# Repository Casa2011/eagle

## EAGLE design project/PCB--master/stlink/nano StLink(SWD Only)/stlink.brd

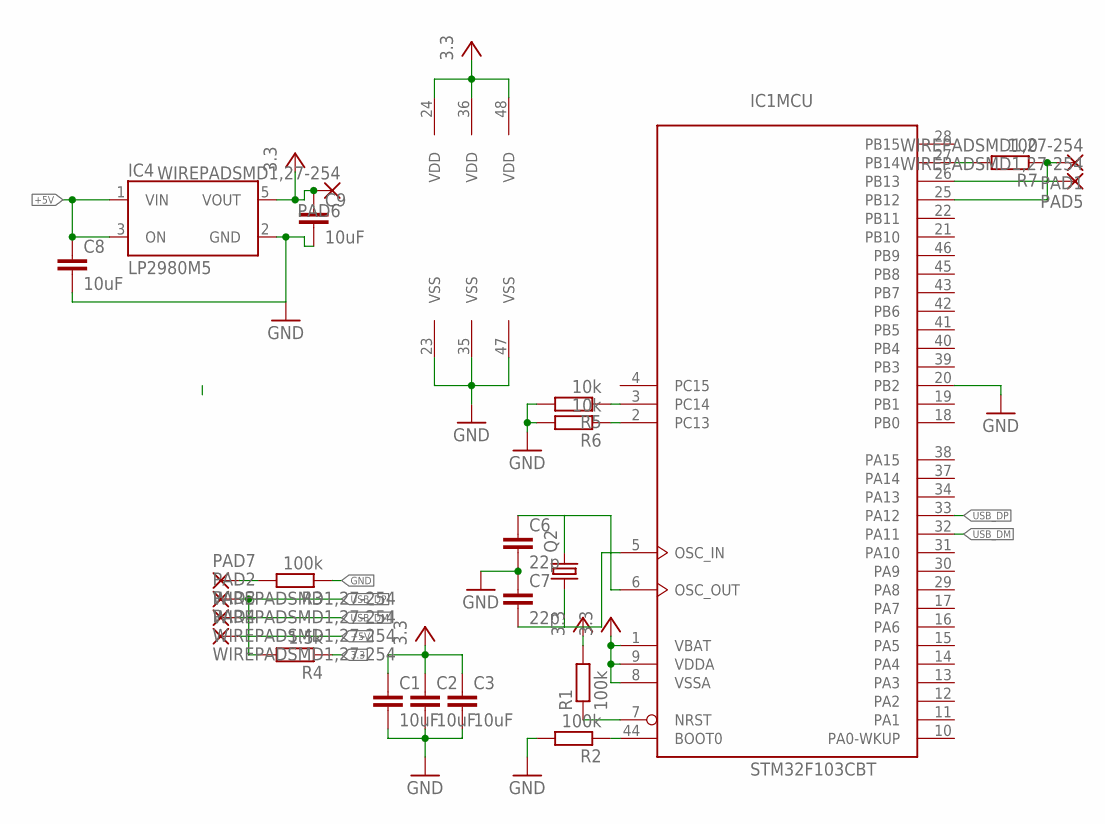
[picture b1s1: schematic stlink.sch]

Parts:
C1, C2, C3, C8, C9: 10uF; C0805
C6, C7: 22p; C0805
IC1: STM32F103CBT; LQFP48
IC4: LP2980M5; SOT23-5
PAD1, PAD2, PAD3, PAD4, PAD5, PAD6, PAD7: WIREPADSMD1,27-254; SMD1,27-2,54
Q2: CRYSTALCTS406; CTS406
R1, R2, R3: 100k; R0805
R4: 1.5k; R0805
R5, R6: 10k; R0805
R7: 100; R0805

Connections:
3.3: R4.1
+5V: C8.1, IC4.1 (VIN), IC4.3 (ON), PAD4.1
GND: C1.2, C2.2, C3.2, C6.2, C7.1, C8.2, C9.2, IC1.20 (PB2), IC1.23 (VSS), IC1.35 (VSS), IC1.47 (VSS), IC4.2 (GND), R2.2, R3.1, R5.2, R6.2
unnamed: C6.1, IC1.6 (OSC_OUT), Q2.3 (2)
unnamed: IC1.7 (NRST), R1.1
unnamed: C7.2, IC1.5 (OSC_IN), Q2.1
unnamed: IC1.44 (BOOT0), R2.1
unnamed: IC1.27 (PB14), R7.2
unnamed: IC1.26 (PB13), PAD5.1
unnamed: PAD7.1, R3.2
unnamed: IC1.3 (PC14), R5.1
unnamed: IC1.2 (PC13), R6.1
unnamed: IC1.25 (PB12), PAD1.1, R7.1
USB_DM: IC1.32 (PA11), PAD3.1
USB_DP: IC1.33 (PA12), PAD2.1, R4.2
VCC: C1.1, C2.1, C3.1, C9.1, IC1.1 (VBAT), IC1.8 (VSSA), IC1.9 (VDDA), IC1.24 (VDD), IC1.36 (VDD), IC1.48 (VDD), IC4.5 (VOUT), PAD6.1, R1.2

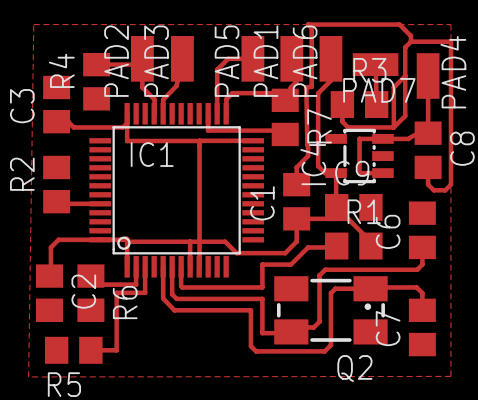
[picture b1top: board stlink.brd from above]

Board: 2 copper layers, 24 parts (0 on the bottom side), 15 nets.

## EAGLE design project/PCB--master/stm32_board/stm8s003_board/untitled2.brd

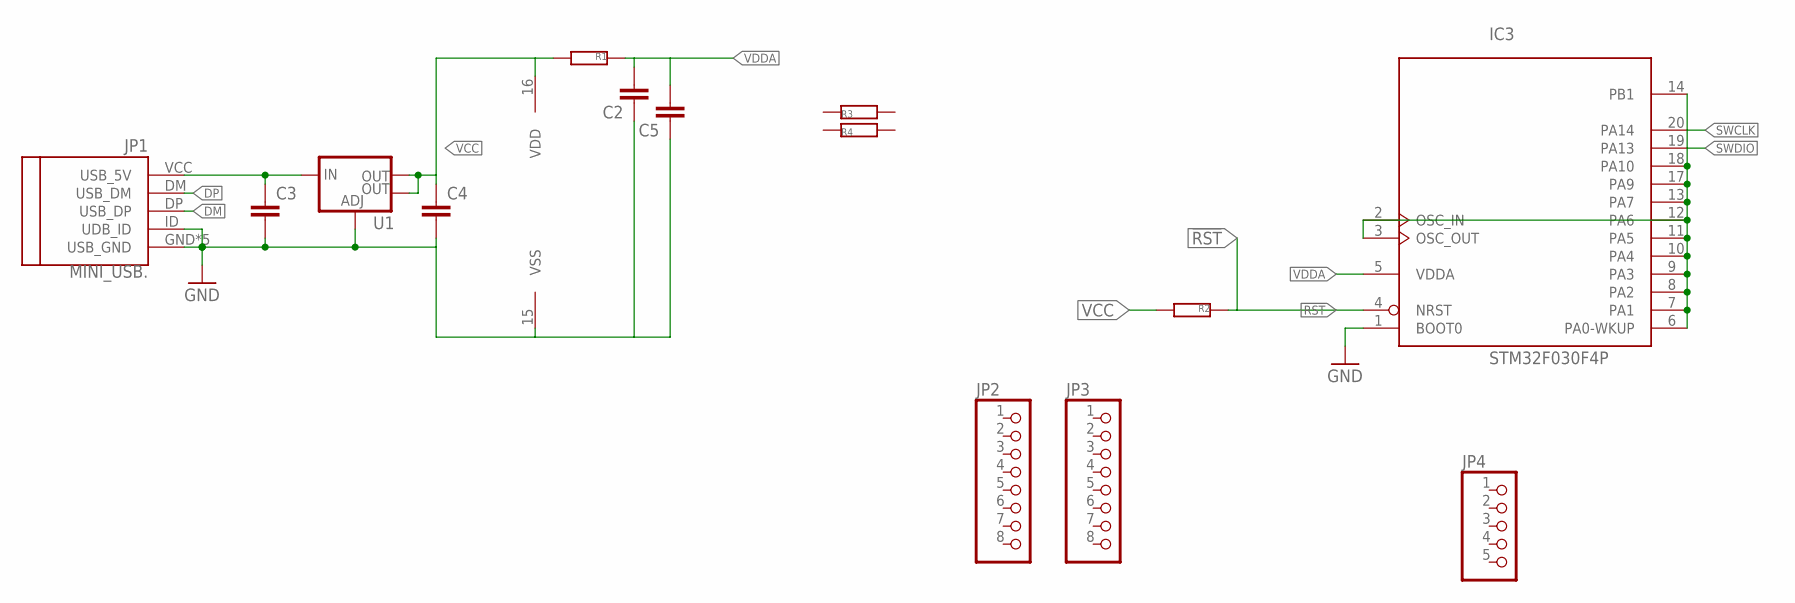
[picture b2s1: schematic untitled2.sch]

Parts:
C2, C3, C4, C5: CC0805; C0805
IC3: STM32F030F4P; TSSOP20-I
JP1: MINI_USB.; 32005-201
JP2, JP3: PINHD-1X08_2.54; 1X08
JP4: PINHD-1X05_2.54; 1X05
R1, R2: R0603; 0603
R3, R4: R0805
U1: V_REG_LM1117SOT223; SOT223

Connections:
5V: C3.1, JP1.VCC (USB_5V), U1.3 (IN)
!RST: IC3.4 (NRST), R2.1
DM: JP1.DP (USB_DP)
DP: JP1.DM (USB_DM)
GND: C2.1, C3.2, C4.2, C5.1, IC3.1 (BOOT0), IC3.15 (VSS), JP1.GND (USB_GND), JP1.ID (UDB_ID), JP1.M1 (USB_GND), JP1.M2 (USB_GND), JP1.M3 (USB_GND), JP1.M4 (USB_GND), U1.1 (ADJ)
unnamed: IC3.2 (OSC_IN), IC3.3 (OSC_OUT), IC3.6 (PA0-WKUP), IC3.7 (PA1), IC3.8 (PA2), IC3.9 (PA3), IC3.10 (PA4), IC3.11 (PA5), IC3.12 (PA6), IC3.13 (PA7), IC3.14 (PB1), IC3.17 (PA9), IC3.18 (PA10)
SWCLK: IC3.20 (PA14)
SWDIO: IC3.19 (PA13)
VCC: C4.1, IC3.16 (VDD), R1.2, R2.2, U1.2 (OUT), U1.4 (OUT)
VDDA: C2.2, C5.2, IC3.5 (VDDA), R1.1

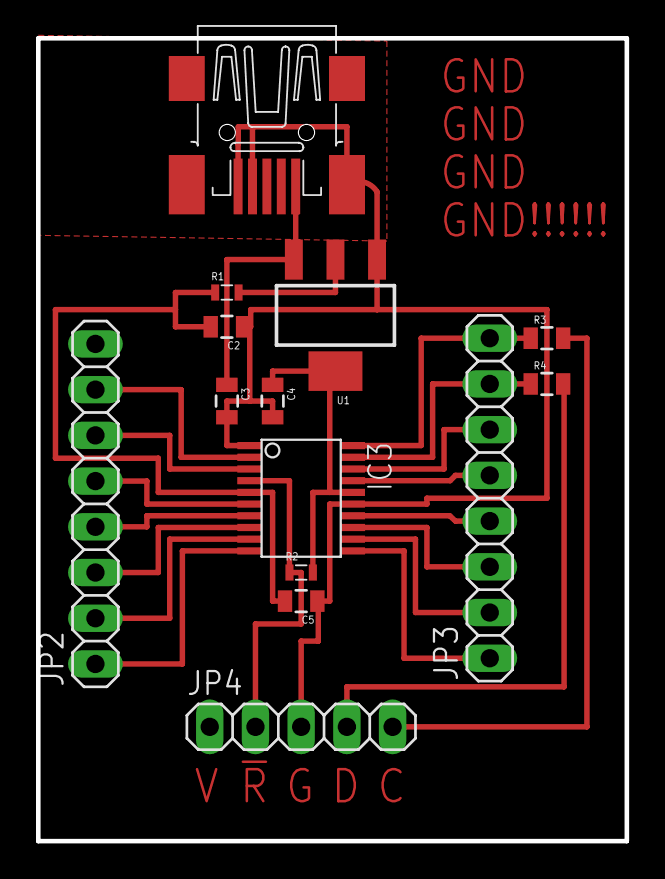
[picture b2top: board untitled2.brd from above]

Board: 2 copper layers, 32.7 x 44.6 mm, 14 parts (0 on the bottom side), 6 nets.

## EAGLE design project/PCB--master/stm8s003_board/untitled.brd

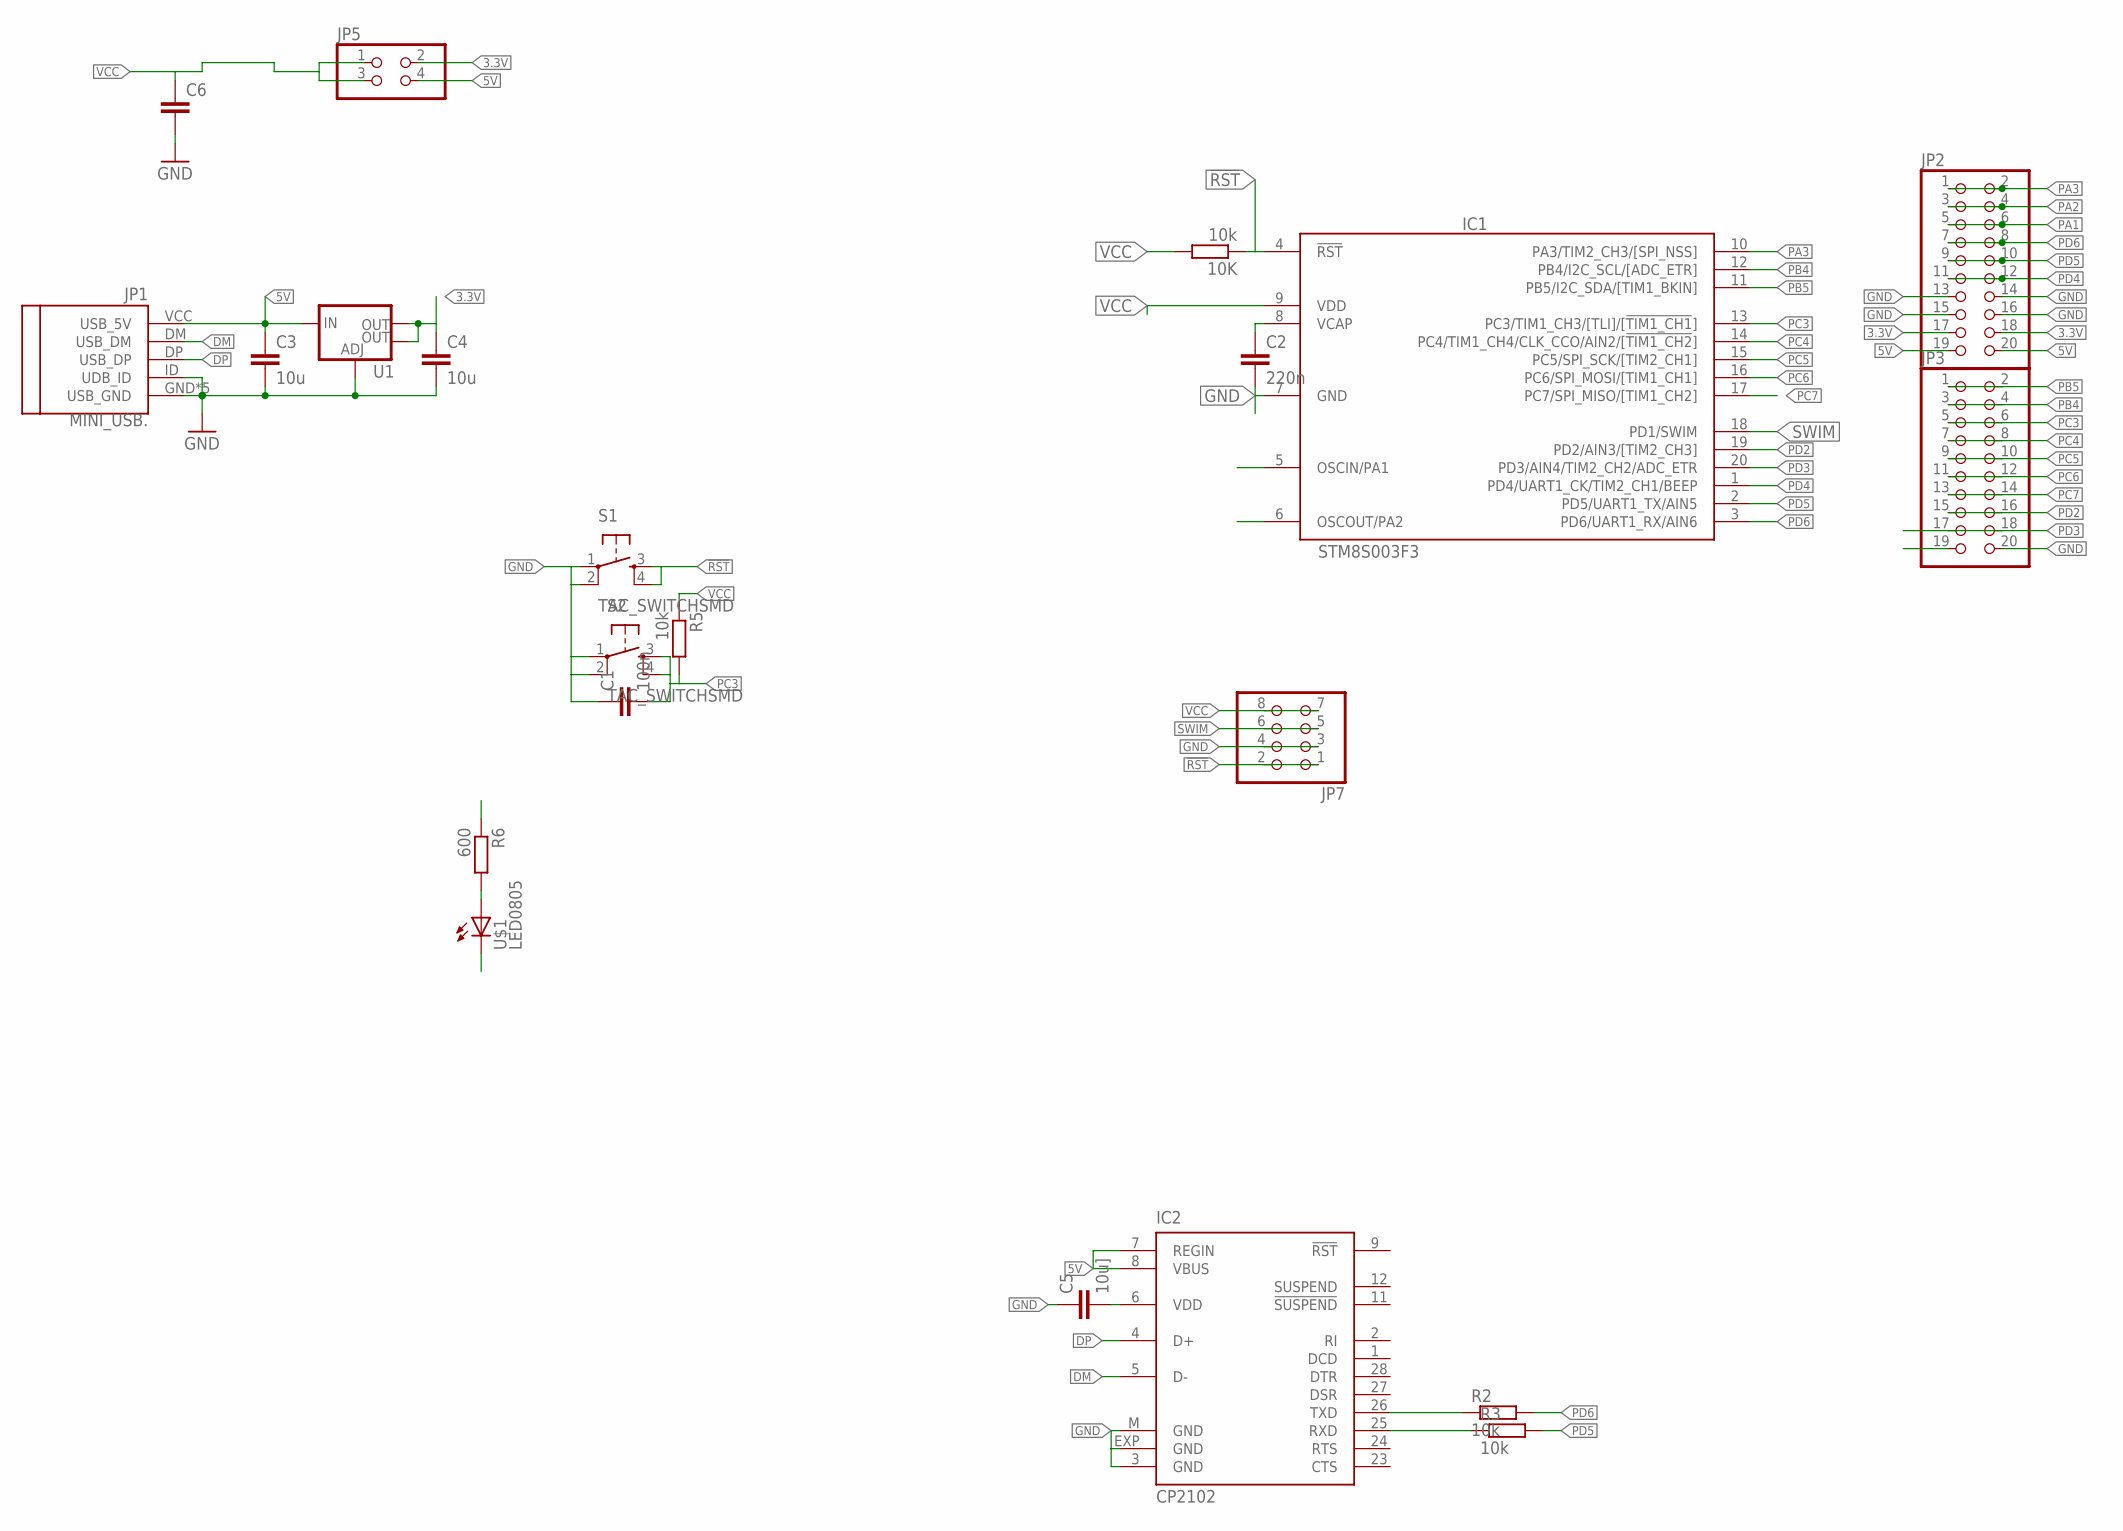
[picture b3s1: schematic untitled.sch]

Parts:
10K: 10k; 0603
C1: 100n; C0805
C2: 220n; C0603
C3, C4: 10u; C0805
C5: 10u]; C0603
C6: CC0805; C0805
IC1: STM8S003F3; TSSOP20
IC2: CP2102; MLP28
JP1: MINI_USB.; 32005-201
JP2, JP3: PINHD-2X10_2.54-SMD; 2X10SMD
JP5: PINHD-2X02_2.54-SMD; 2X02SMD
JP7: PINHD-2X04_2.54-SMD; 2X04SMD
R2, R3, R5: 10k; 0603
R6: 600; 0603
S1, S2: TAC_SWITCHSMD; TACTILE-SWITCH-SMD
U1: V_REG_LM1117SOT223; SOT223
U$1: LED0805; 0805-LED

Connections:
1: IC2.26 (TXD), R2.1
2: IC2.25 (RXD), R3.1
3.3V: C4.1, JP2.17, JP2.18, JP5.2, U1.2 (OUT), U1.4 (OUT)
5V: C3.1, IC2.7 (REGIN), IC2.8 (VBUS), JP1.VCC (USB_5V), JP2.19, JP2.20, JP5.4, U1.3 (IN)
!RST: 10K.1, IC1.4 (!RST), JP7.1, JP7.2, S1.3, S1.4
DM: IC2.5 (D-), JP1.DM (USB_DM)
DP: IC2.4 (D+), JP1.DP (USB_DP)
GND: C1.1, C2.2, C3.2, C4.2, C5.1, C6.2, IC1.7 (GND), IC2.3 (GND), IC2.EXP (GND), IC2.M (GND), JP1.GND (USB_GND), JP1.ID (UDB_ID), JP1.M1 (USB_GND), JP1.M2 (USB_GND), JP1.M3 (USB_GND), JP1.M4 (USB_GND), JP2.13, JP2.14, JP2.15, JP2.16, JP3.19, JP3.20, JP7.3, JP7.4, S1.1, S1.2, S2.1, S2.2, U1.1 (ADJ), U$1.C
unnamed: C2.1, IC1.8 (VCAP)
unnamed: C5.2, IC2.6 (VDD)
unnamed: R6.2, U$1.A
PA1: IC1.5 (OSCIN/PA1), JP2.5, JP2.6
PA2: IC1.6 (OSCOUT/PA2), JP2.3, JP2.4
PA3: IC1.10 (PA3/TIM2_CH3/[SPI_NSS]), JP2.1, JP2.2
PB4: IC1.12 (PB4/I2C_SCL/[ADC_ETR]), JP3.3, JP3.4
PB5: IC1.11 (PB5/I2C_SDA/[TIM1_BKIN]), JP3.1, JP3.2
PC3: C1.2, IC1.13 (PC3/TIM1_CH3/[TLI]/[!TIM1_CH1!]), JP3.5, JP3.6, R5.2, S2.3, S2.4
PC4: IC1.14 (PC4/TIM1_CH4/CLK_CCO/AIN2/[!TIM1_CH2!]), JP3.7, JP3.8
PC5: IC1.15 (PC5/SPI_SCK/[TIM2_CH1]), JP3.9, JP3.10
PC6: IC1.16 (PC6/SPI_MOSI/[TIM1_CH1]), JP3.11, JP3.12
PC7: IC1.17 (PC7/SPI_MISO/[TIM1_CH2]), JP3.13, JP3.14
PD2: IC1.19 (PD2/AIN3/[TIM2_CH3]), JP3.15, JP3.16
PD3: IC1.20 (PD3/AIN4/TIM2_CH2/ADC_ETR), JP3.17, JP3.18
PD4: IC1.1 (PD4/UART1_CK/TIM2_CH1/BEEP), JP2.11, JP2.12
PD5: IC1.2 (PD5/UART1_TX/AIN5), JP2.9, JP2.10, R3.2
PD6: IC1.3 (PD6/UART1_RX/AIN6), JP2.7, JP2.8, R2.2
SWIM: IC1.18 (PD1/SWIM), JP7.5, JP7.6
VCC: 10K.2, C6.1, IC1.9 (VDD), JP5.1, JP5.3, JP7.7, JP7.8, R5.1, R6.1

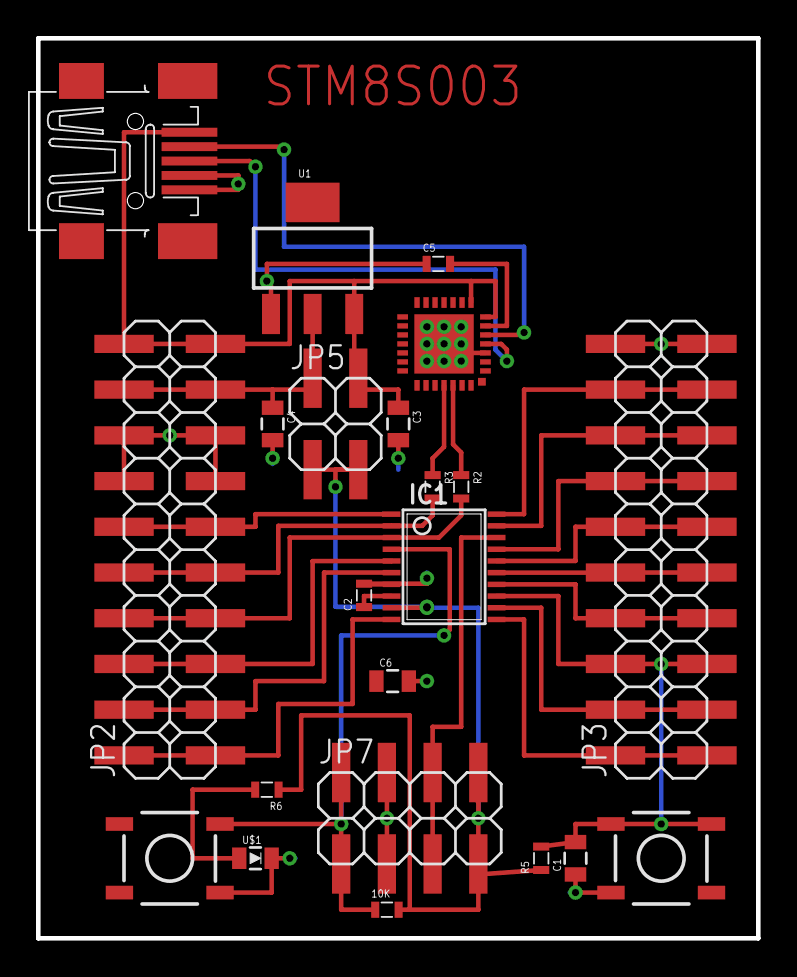
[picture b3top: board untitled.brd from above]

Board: 2 copper layers, 40.0 x 50.0 mm, 22 parts (0 on the bottom side), 28 nets.

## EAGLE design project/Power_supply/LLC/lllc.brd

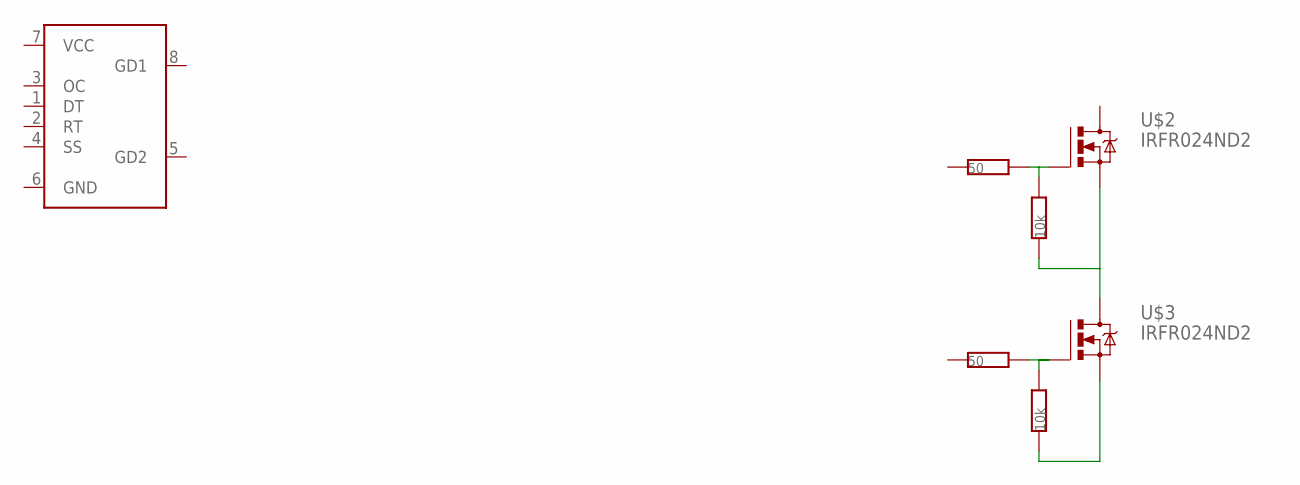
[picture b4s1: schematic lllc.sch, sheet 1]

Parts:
R1, R2: 50; R0805
R3, R4: 10k; R0805
U$1: TPS92020; SO08
U$2, U$3: IRFR024ND2; D2PACK

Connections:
unnamed: R3.1, U$2.3 (S), U$3.2 (D)
unnamed: R1.2, R3.2, U$2.1 (G)
unnamed: R2.2, R4.2, U$3.1 (G)
unnamed: R4.1, U$3.3 (S)

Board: 2 copper layers, 7 parts (0 on the bottom side), 4 nets, no tracks yet.

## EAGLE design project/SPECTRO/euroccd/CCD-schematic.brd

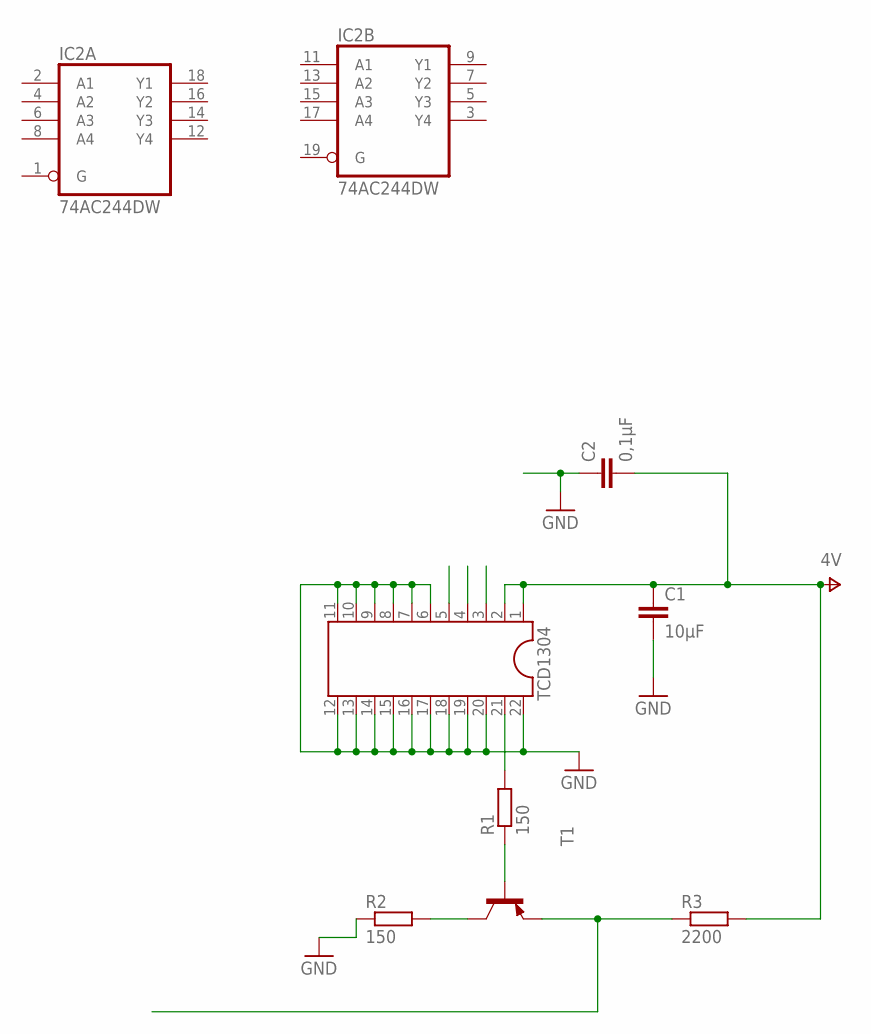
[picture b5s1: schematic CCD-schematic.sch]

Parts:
C1: 10µF; 0805
C2: 0,1µF; 0805
IC2: 74AC244DW; SO20W
R1, R2: 150; 0603
R3: 2200; 0603
T1: -PNP-SOT23-EBC; SOT23-EBC
TCD1304: DIL22-4

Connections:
GND: C1.2, C2.1, IC2.10 (GND), R2.1, TCD1304.6, TCD1304.7, TCD1304.8, TCD1304.9, TCD1304.10, TCD1304.11, TCD1304.12, TCD1304.13, TCD1304.14, TCD1304.15, TCD1304.16, TCD1304.17, TCD1304.18, TCD1304.19, TCD1304.20, TCD1304.22
unnamed: R3.1, T1.E
unnamed: R1.1, T1.B
unnamed: R1.2, TCD1304.21
unnamed: R2.2, T1.C
V+: C1.1, C2.2, R3.2, TCD1304.1, TCD1304.2
VCC: IC2.20 (VCC)

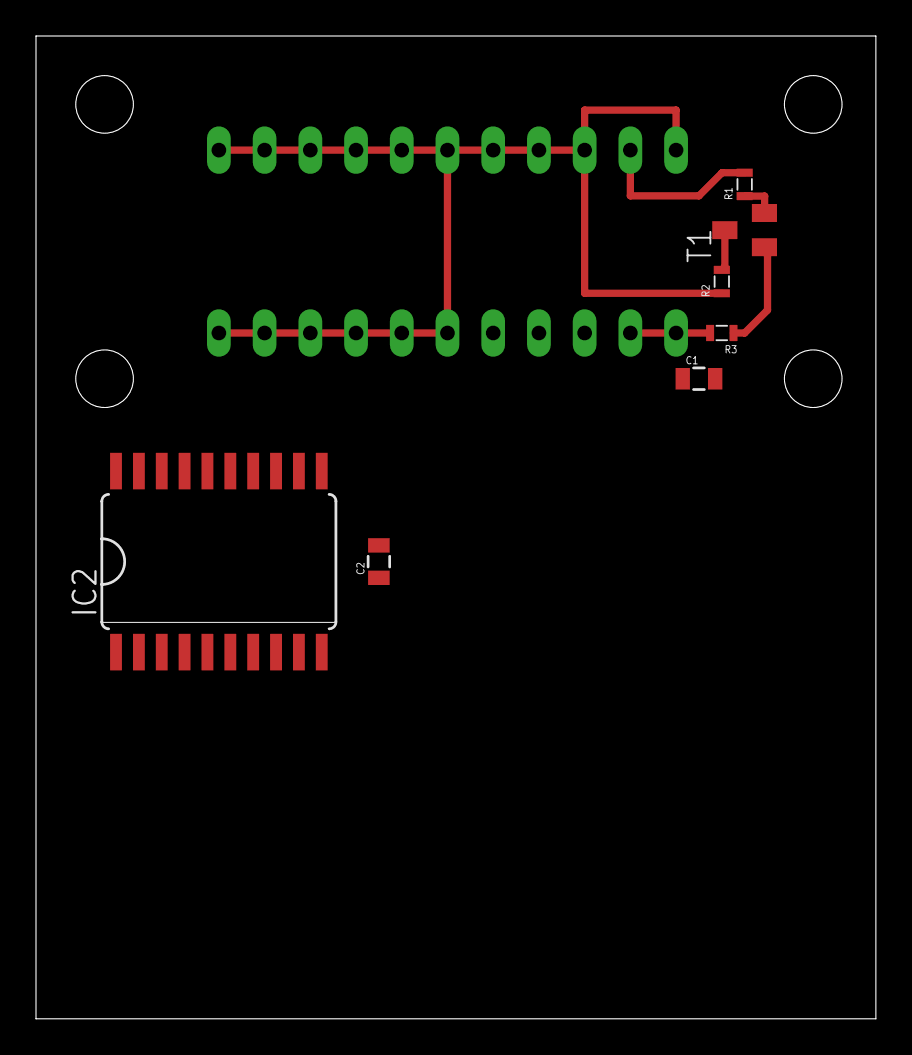
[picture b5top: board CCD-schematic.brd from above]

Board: 2 copper layers, 46.7 x 54.6 mm, 8 parts (1 on the bottom side), 6 nets.

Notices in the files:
parts and their libraries:
SparkFun-Aesthetics: Licensing: Creative Commons ShareAlike 4.0 International - https://creativecommons.org/licenses/by-sa/4.0
